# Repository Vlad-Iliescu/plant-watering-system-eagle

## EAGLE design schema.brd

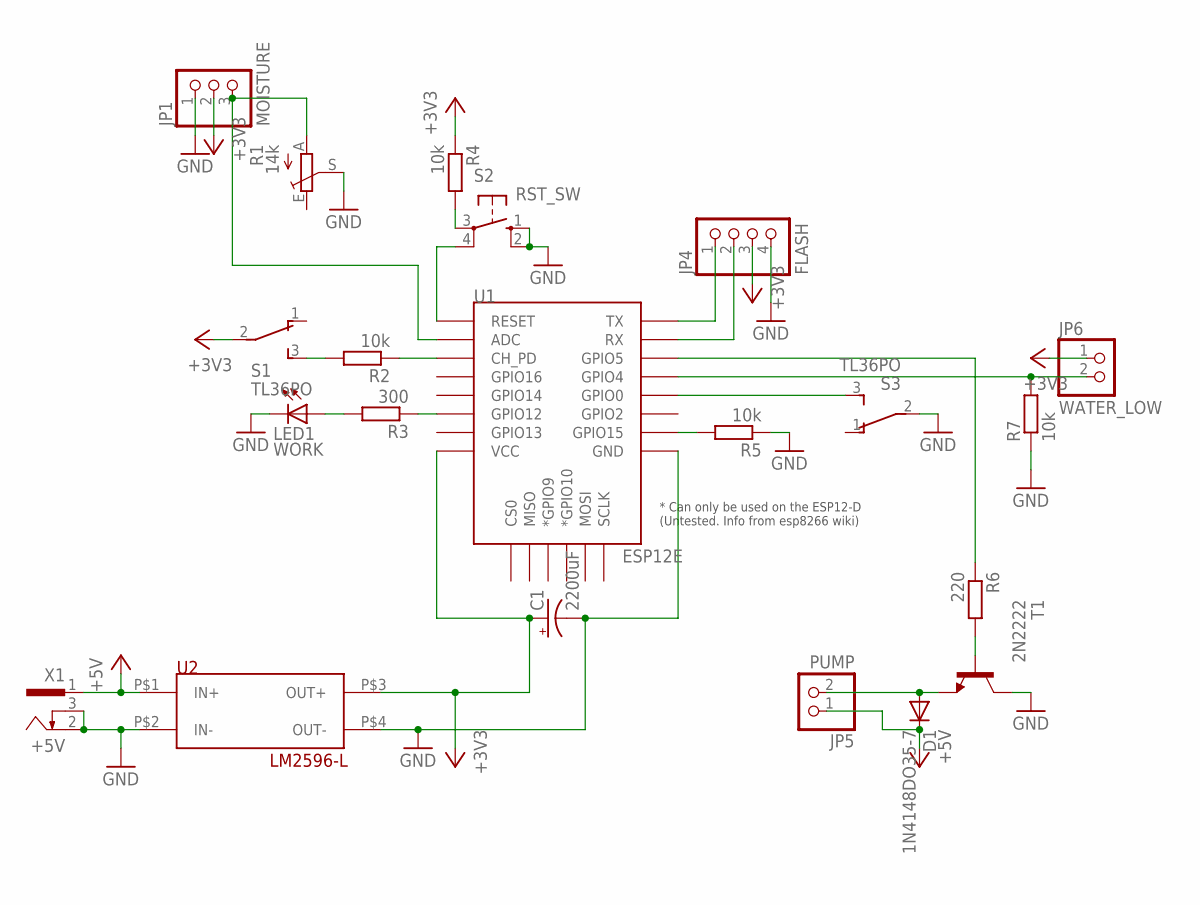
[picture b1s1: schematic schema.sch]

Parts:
C1: 2200uF; CPOL-RADIAL-100UF-25V
D1: 1N4148DO35-7; DO35-7
JP1: MOISTURE; 1X03
JP4: FLASH; 1X04
JP5: PUMP; 1X02
JP6: WATER_LOW; 1X02
LED1: WORK; LED3MM
R1: 14k; CA6V
R2, R4, R5, R7: 10k; 0309V
R3: 300; 0309V
R6: 220; 0309V
S1, S3: TL36PO; TL3XPO
S2: RST_SW; B3F-10XX
T1: 2N2222; TO18
U1: ESP12E; ESP12E-SMD
U2: LM2596-L
X1: +5V; 733989-5

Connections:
+3V3: C1.1 (+), JP1.2, JP4.3, JP6.1, R4.1, S1.2, U1.VCC, U2.P$3 (OUT+)
+5V: D1.C, JP5.1, U2.P$1 (IN+), X1.1
ADC: JP1.3, R1.A, U1.ADC
CH_PD: R2.1, U1.CH_PD
CH_PD_S: R2.2, S1.3 (S)
GND: C1.2 (-), JP1.1, JP4.4, LED1.K (C), R1.S, R5.1, R7.1, S2.1 (S), S2.2 (S1), S3.2, T1.3 (C), U1.GND, U2.P$2 (IN-), U2.P$4 (OUT-), X1.2, X1.3
GPIO0: S3.3 (S), U1.GPIO0
GPIO4: JP6.2, R7.2, U1.GPIO4
GPIO5: R6.1, U1.GPIO5
GPIO5_T: R6.2, T1.2 (B)
GPIO12: R3.1, U1.GPIO12
GPIO12D: LED1.A, R3.2
GPIO15: R5.2, U1.GPIO15
PUMP_GND: D1.A, JP5.2, T1.1 (E)
RST: S2.4 (P1), U1.RESET
RST_R: R4.2, S2.3
RX: JP4.2, U1.RXD0 (RX)
TX: JP4.1, U1.TXD0 (TX)

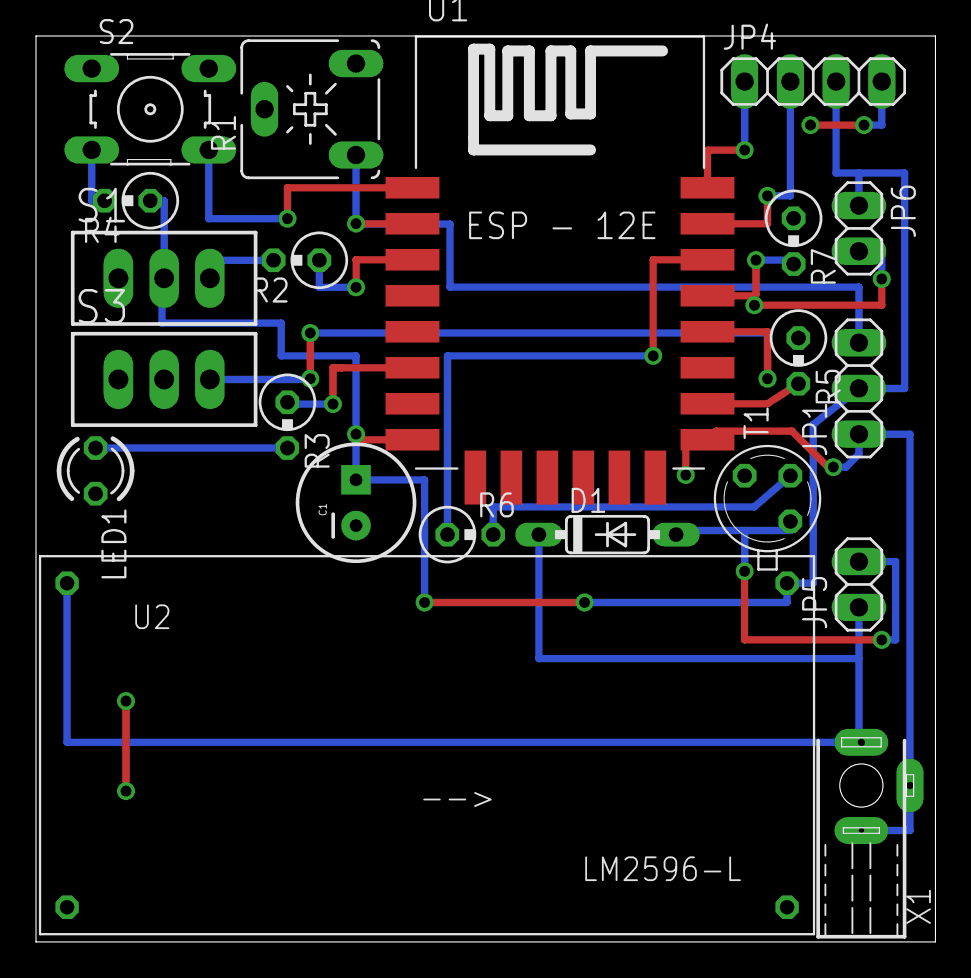
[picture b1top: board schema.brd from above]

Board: 2 copper layers, 50.0 x 50.3 mm, 21 parts (0 on the bottom side), 18 nets.

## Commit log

2017-03-11 Version 2
2017-03-12 Circuit Update
2017-03-14 Changed Buck
2017-04-12 Added PDF schema
2017-05-14 new Eagle version

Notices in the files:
parts and their libraries:
SparkFun-Capacitors: Licensing: Creative Commons ShareAlike 4.0 International - https://creativecommons.org/licenses/by-sa/4.0
